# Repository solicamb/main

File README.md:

# main
The repository for the code associated with the devices done by Solicamb.

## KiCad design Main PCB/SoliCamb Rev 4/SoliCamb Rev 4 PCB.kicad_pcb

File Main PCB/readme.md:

Link to BOM: https://octopart.com/bom-tool/TTlpAv4m

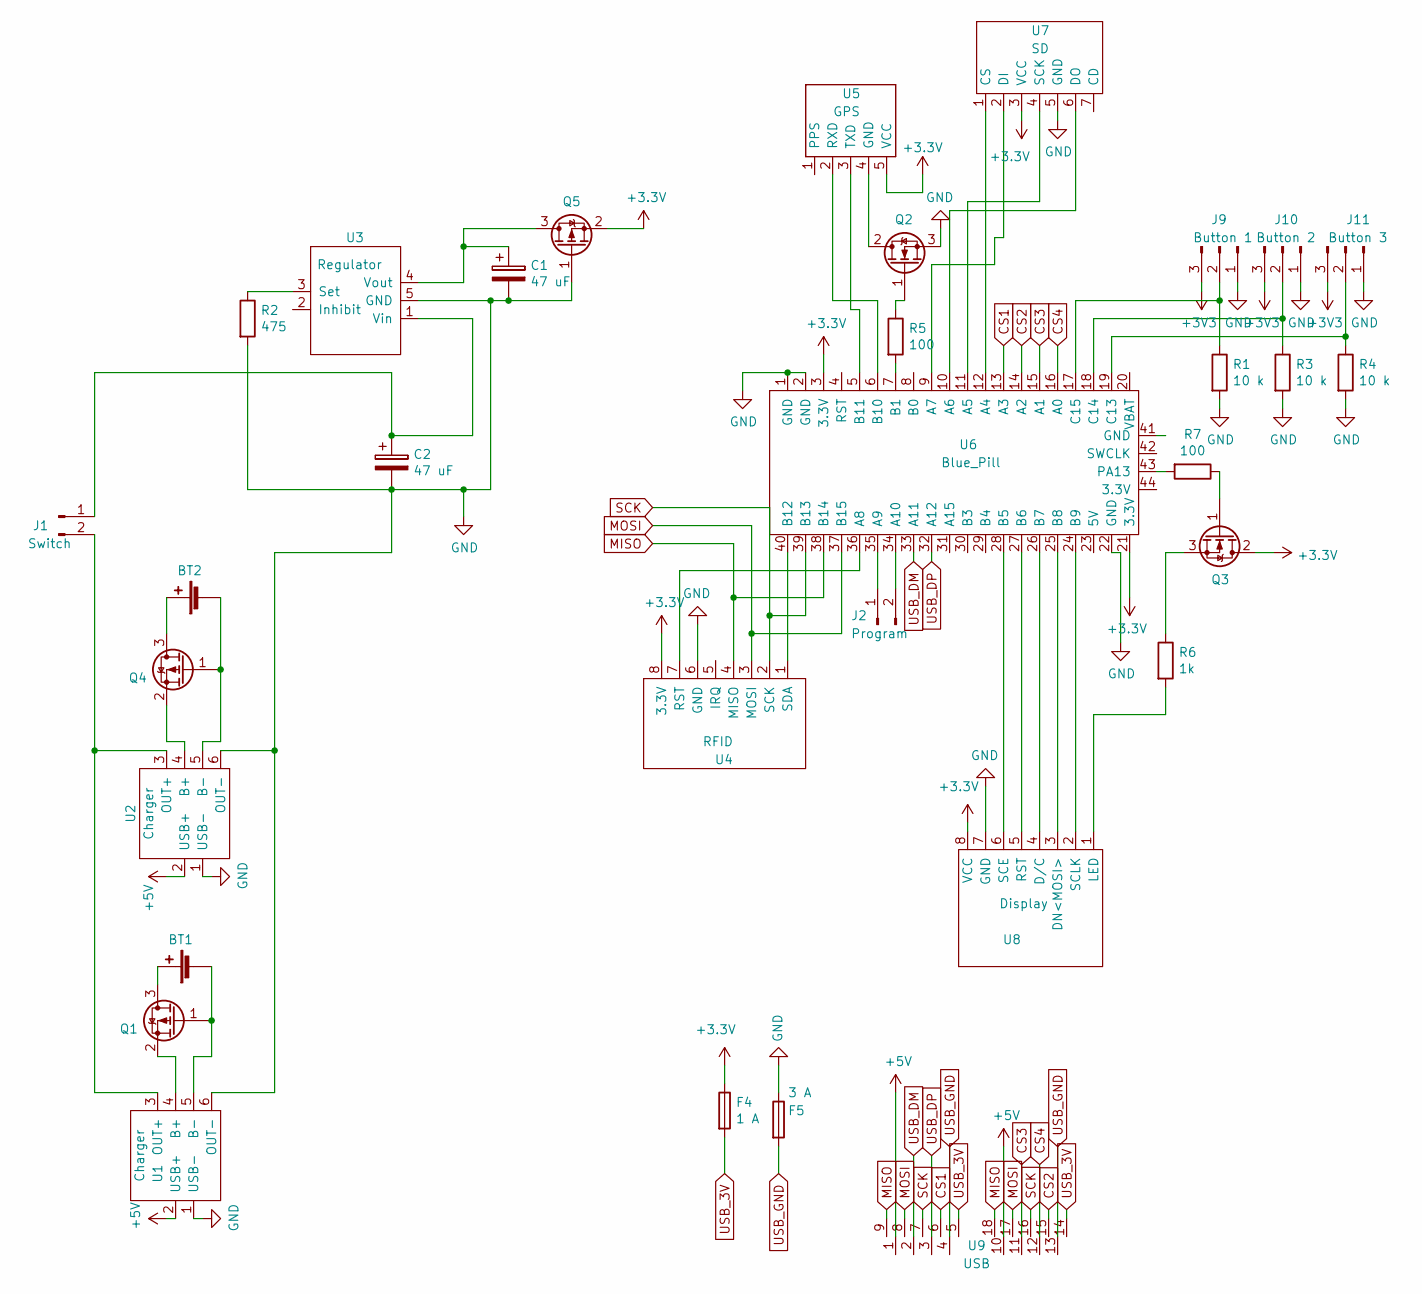
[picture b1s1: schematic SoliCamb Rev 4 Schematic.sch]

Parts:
BT1, BT2: Battery_Cell; BatteryHolder_Keystone_1042_1x18650
C1, C2: 47 uF; CP_Radial_D4.0mm_P2.00mm
F4: 1 A; R_1812_4532Metric_Pad1.30x3.40mm_HandSolder
F5: 3 A; R_1812_4532Metric_Pad1.30x3.40mm_HandSolder
J1: Switch; PinHeader_1x02_P2.54mm_Vertical_SMD_Pin1Left
J2: Program; PinHeader_1x02_P2.54mm_Vertical_SMD_Pin1Left
J9: Button 1; PinHeader_1x03_P2.54mm_Vertical_SMD_Pin1Left
J10: Button 2; PinHeader_1x03_P2.54mm_Vertical_SMD_Pin1Left
J11: Button 3; PinHeader_1x03_P2.54mm_Vertical_SMD_Pin1Left
Q1, Q4, Q5: Q_PMOS_GSD; SOT-23_Handsoldering
Q2, Q3: Q_NMOS_GDS; SOT-23_Handsoldering
R1, R3: 10 k; R_Axial_DIN0309_L9.0mm_D3.2mm_P12.70mm_Horizontal
R2: 475; R_Axial_DIN0309_L9.0mm_D3.2mm_P12.70mm_Horizontal
R4: 10 k; R_Axial_DIN0411_L9.9mm_D3.6mm_P12.70mm_Horizontal
R5, R7: 100; R_Axial_DIN0309_L9.0mm_D3.2mm_P12.70mm_Horizontal
R6: 1k; R_Axial_DIN0309_L9.0mm_D3.2mm_P12.70mm_Horizontal
U1, U2: Charger; Battery_Charger
U3: Regulator
U4: RFID; PinHeader_1x08_P2.54mm_Vertical
U5: GPS
U6: Blue_Pill; Blue_pill
U7: SD; PinHeader_1x07_P2.54mm_Vertical
U8: Display
U9: USB

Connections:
+5V: U1.2 (USB+), U2.2 (USB+), U9.1, U9.10
CS1: U6.13 (A3), U9.6
CS2: U6.14 (A2), U9.15
CS3: U6.15 (A1), U9.11
CS4: U6.16 (A0), U9.12
GND: C1.2, C2.2, F5.1, J9.1, J10.1, J11.1, Q2.3 (S), Q5.1 (G), R1.2, R2.2, R3.2, R4.2, U1.1 (USB-), U1.6 (OUT-), U2.1 (USB-), U2.6 (OUT-), U3.5 (GND), U4.6 (GND), U6.1 (GND), U6.2 (GND), U6.22 (GND), U7.5 (GND), U8.7 (GND)
MISO: U4.4 (MISO), U6.38 (B14), U9.9, U9.18
MOSI: U4.3 (MOSI), U6.37 (B15), U9.8, U9.17
unnamed: BT1.1 (+), Q1.3 (D)
unnamed: BT1.2 (-), Q1.1 (G), U1.5 (B-)
unnamed: BT2.1 (+), Q4.3 (D)
unnamed: BT2.2 (-), Q4.1 (G), U2.5 (B-)
unnamed: C1.1, Q5.3 (D), U3.4 (Vout)
unnamed: C2.1, J1.1, U3.1 (Vin)
unnamed: J1.2, U1.3 (OUT+), U2.3 (OUT+)
unnamed: J2.1, U6.35 (A9)
unnamed: J2.2, U6.34 (A10)
unnamed: J9.2, R1.1, U6.17 (C15)
unnamed: J10.2, R3.1, U6.18 (C14)
unnamed: J11.2, R4.1, U6.19 (C13)
unnamed: Q1.2 (S), U1.4 (B+)
unnamed: Q2.1 (G), R5.1
unnamed: Q2.2 (D), U5.4 (GND)
unnamed: Q3.1 (G), R7.1
unnamed: Q3.3 (S), R6.1
unnamed: Q4.2 (S), U2.4 (B+)
unnamed: R2.1, U3.3 (Set)
unnamed: R5.2, U6.7 (B1)
unnamed: R6.2, U8.1 (LED)
unnamed: R7.2, U6.43 (PA13)
unnamed: U4.1 (SDA), U6.40 (B12)
unnamed: U4.7 (RST), U6.36 (A8)
unnamed: U5.2 (RXD), U6.6 (B10)
unnamed: U5.3 (TXD), U6.5 (B11)
unnamed: U6.9 (A7), U7.2 (DI)
unnamed: U6.10 (A6), U7.6 (DO)
unnamed: U6.11 (A5), U7.4 (SCK)
unnamed: U6.12 (A4), U7.1 (CS)
unnamed: U6.24 (B9), U8.2 (SCLK)
unnamed: U6.25 (B8), U8.3 (DN<MOSI>)
unnamed: U6.26 (B7), U8.4 (D/C)
unnamed: U6.27 (B6), U8.5 (RST)
unnamed: U6.28 (B5), U8.6 (SCE)
SCK: U4.2 (SCK), U6.39 (B13), U9.7, U9.16
USB_3V: F4.2, U9.5, U9.14
USB_DM: U6.33 (A11), U9.2
USB_DP: U6.32 (A12), U9.3
USB_GND: F5.2, U9.4, U9.13

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
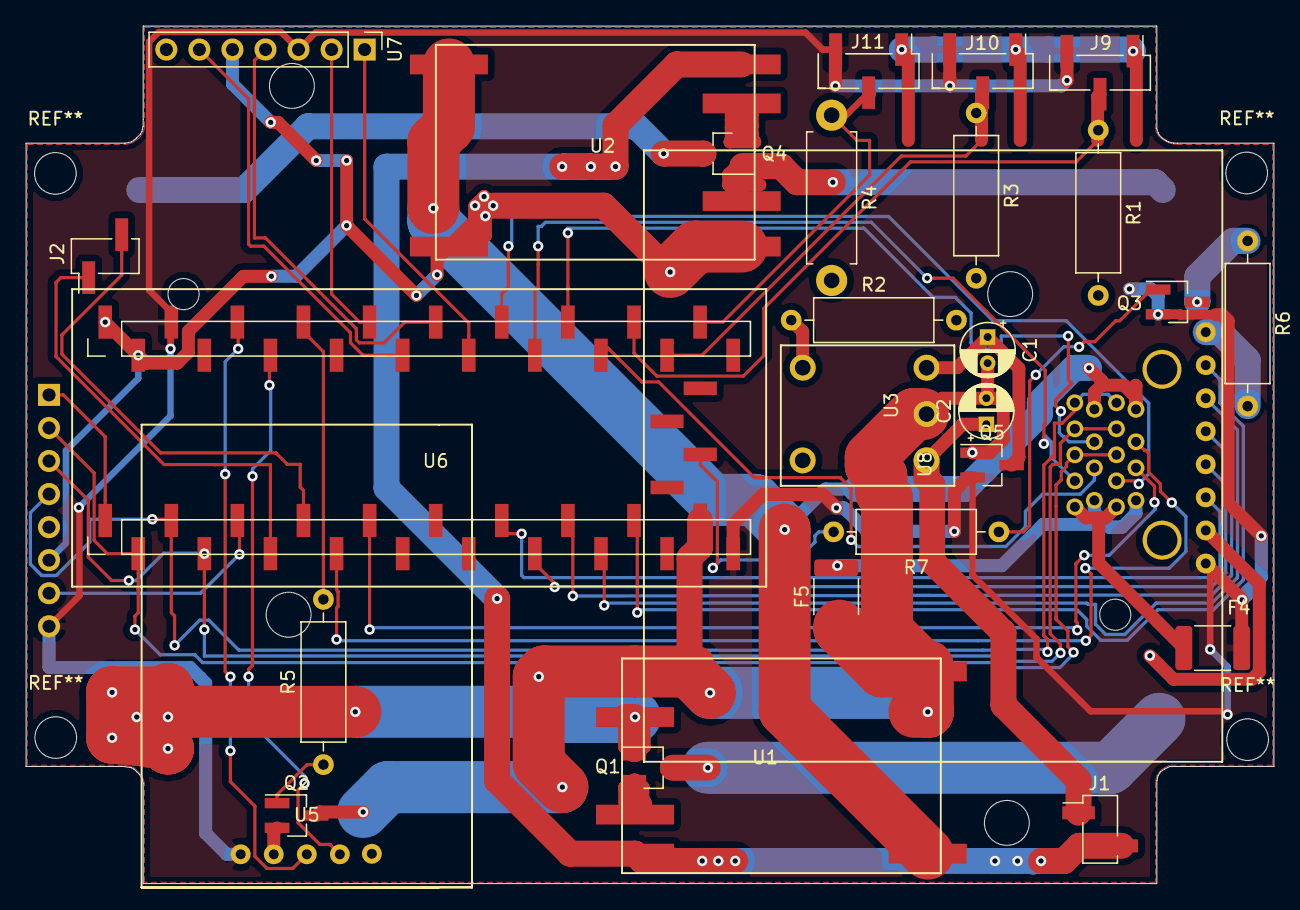
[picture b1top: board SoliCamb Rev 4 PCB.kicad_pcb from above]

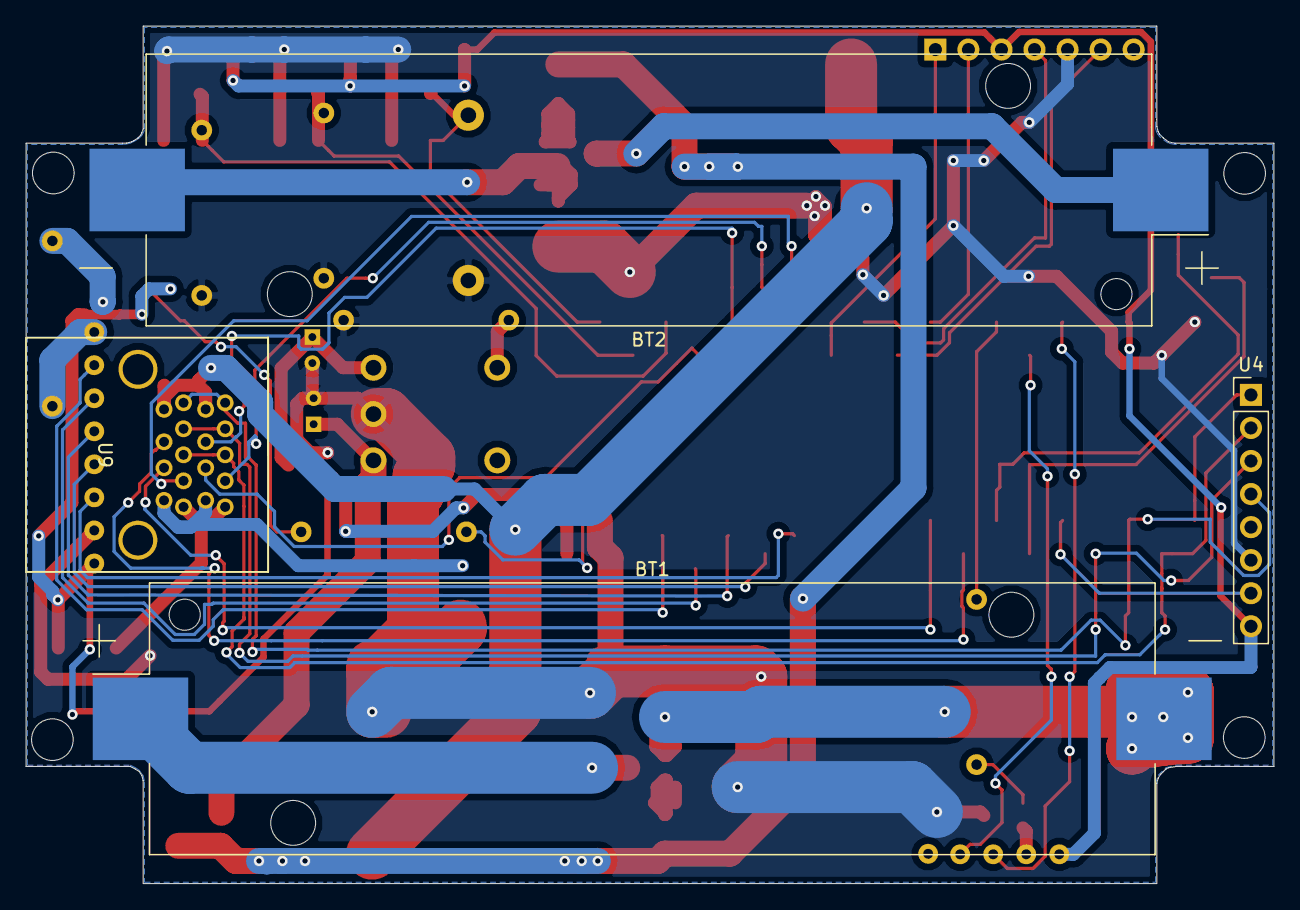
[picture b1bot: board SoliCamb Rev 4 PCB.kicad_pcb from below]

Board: 2 copper layers, 95.9 x 65.9 mm, 32 parts (4 on the bottom side), 49 nets.

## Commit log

2019-07-16 updated the readme with basic info
2019-07-16 Initial commit of the README for the moisture probe subfolder
2019-07-16 Initial commit of the code files
2019-07-19 Update README.md
    Added installation instructions for Windows and Unix users
2019-07-25 Renamed files according to Arduino naming convention (file and folder name identical)
2019-07-25 Rename to Arduino naming conventions File and folder name must be identical
2019-07-25 .gitignore: Ignore moisture-probe/plot/data dir These files contain measurement data not relevant to this code repository
2019-07-25 Initial commit for data analysis and plotting file This takes all .csv files (as command line arguments) from what the live_plot.py script produced, and turns them into plots for visual analysis. Cal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
2019-07-29 Duplicate Arduino code: begin porting to bluepill
2019-07-29 Added pinout image
2019-07-29 Allow different ADC full scale voltage; resolution
2019-07-30 Initial Commit
    Added standard Arduino library templates
2019-07-30 Changed DOWNSAMPLING value
2019-07-30 Increased downsampling again Plot was still lagging on a MacBook Air plotting
2019-07-30 Improved comments and explanations
2019-07-30 Commenting; better variable naming
2019-07-31 Typo
2019-07-31 Initial commit for the production code This is what will run on the slave device (bluepill, not Arduino). Still early stage but basic communication is working
2019-08-01 Disabled waiting for START (bluepill issue) See comment in file for reasoning
2019-08-01 Constrain output value (for debugging display)
2019-08-01 Better help messages for user
2019-08-01 .gitignore: graph plots
2019-08-01 Minimum Working Example From http://www.gammon.com.au/spi
2019-08-01 Minimum Working Handshake
2019-08-01 Functioning message passing routine with string support
2019-08-02 Message passing with multiple data types. Added header files
2019-08-02 Branch to move towards final code Not in main to retain working, unchanged version
2019-08-02 Moved communication protocol to class space
2019-08-02 Completed Class Hierarchy. Untested
2019-08-03 Stubbed out functions for program logic flow
2019-08-05 Moved base class into composition to avoided the dreaded diamond
    Potential problem: composed class Communicative needs to know or recieve ChipSelect. To know to be redundant, to receive is to have polymorphic issues or reintroduce diamondality.
2019-08-05 Fixed Compile-time errors
2019-08-05 Removed magic numbers from Master side
2019-08-06 Created monolithic 'Master' class to be used by slave
    Designed to allow slave to communicate with master and manage data/sets of instructions
2019-08-06 Comments
2019-08-07 Branching here to work on STM32 platforms
2019-08-07 Updated downsampling; small refactoring
2019-08-07 Interactive step-by-step measurement w/ user GUI
2019-08-07 Implemented moisture level (wetness) stub code
2019-08-07 Removed old development version (superseded)
2019-08-07 Updated DOWNSAMPLING on production code
2019-08-07 Basic STM32, interrupt driven SPI
    Can't get the native spi_rx interrupt to run. So using attachInterrupt() on the SS pin
2019-08-08 Refactoring. Pseudocode for moisture retention alg
2019-08-08 Refactoring, comments
2019-08-08 Removed unused variable
2019-08-08 Messy pseudo-unit test sketch
    Master sketch tests most of the Master-interface and, by extension, the slave functionality. Needs cleaning
2019-08-08 Encapsulated interrupt; messy
2019-08-08 Encapsulated Interrupt; cleaned up
2019-08-08 minor houskeeping
2019-08-08 Example Code to demonstrate OOPI
2019-08-08 Added Slave start state to allow listening for permission to begin
2019-08-08 Minor housekeeping
2019-08-09 Changed folder name
2019-08-09 Refactoring. Comments; Skipped another SPI transfer in debugging mode
2019-08-12 Added doxygen comments
2019-08-12 Removed unnecessary files
2019-08-12 Implemented moist. ret. algorithm framework Also included delay before initial SPI communication. Sometimes, USB connection caused bouncing issues causing master and slave to loose sync
2019-08-12 Updated wetness thresholds
2019-08-12 Extended wetness meas. to three depths
2019-08-12 GitBook: [master] 2 pages modified
2019-08-12 First draft implementation: moist. ret. score alg.
2019-08-12 Moisture Retention Algorithm improvements
2019-08-12 Fixed Readme. Sorry about that
2019-08-12 Good run of doxygen -> doxybook
2019-08-12 Repeat documentation markdown generation
2019-08-12 Fixed summary
2019-08-12 Updated OOPI Readme
2019-08-12 Housekeeping
2019-08-13 Added badge
2019-08-13 Updates and bugfixes to MR algorithm
2019-08-16 Soil moisture velocity now in cm/min Idea is to restrict citizen scientist less in the range of readings; have them take several readings to see what range their soil falls into
2019-08-16 Changed signal thresholding to signed comparison
2019-08-16 Create C-3NpH
2019-08-16 Create Immerse Cambridge Summer School
2019-08-17 added PCB, BOM to do
2019-08-19 Initial adaptation of main unit firmware to OOPI
    Data handling still to be implemented
2019-08-24 Added sensor library
